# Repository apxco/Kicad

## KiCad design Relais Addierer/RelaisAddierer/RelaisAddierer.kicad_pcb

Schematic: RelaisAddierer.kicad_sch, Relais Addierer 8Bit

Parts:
A1: RaspberryPi_Pico; RaspberryPi_Pico_Common_Unspecified
C1: 1uF; C_0805_2012Metric_Pad1.18x1.45mm_HandSolder
C2, C3, C4, C5, C6, C7: 100nF; C_0805_2012Metric_Pad1.18x1.45mm_HandSolder
C8, C9, C10, C11, C12: 470uF; CP_Elec_10x12.5
D1, D2, D3, D4, D5, D6, D7, D8, D10, D11, D12, D13, D14, D15, D16, D17, D18, D19, D20, D21, D22, D23, D24, D25, D26, D27, D28, D29, D30, D31, D32, D33: 1N4148WT; D_SOD-523
D9: 1N4007; D_DO-41_SOD81_P10.16mm_Horizontal
J1: Conn_01x08_Pin; PinHeader_1x08_P2.54mm_Vertical
J2: Barrel_Jack; BarrelJack_GCT_DCJ200-10-A_Horizontal
K1, K2, K3, K4, K5, K6, K7, K8, K9, K10, K11, K12, K13, K14, K15, K16, K17, K18, K19, K20, K21, K22, K23, K24, K25, K26, K27, K28, K29, K30, K31, K32: HK19F-DCxxV-SHC; Relay_DPDT_Finder_30.22
R1, R2, R3, R4, R5, R6, R7, R8, R9, R10: 10k; R_0805_2012Metric_Pad1.20x1.40mm_HandSolder
SW1, SW2: RotaryEncoder_Switch; RotaryEncoder_Alps_EC12E-Switch_Vertical_H20mm
U1, U2, U3: TCA9534; TSSOP-16_4.4x5mm_P0.65mm
U4: uA7805; TO-263-2_TabPin1

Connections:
+5V: A1.40 (VBUS), C2.1, C3.1, C4.1, C5.1, C6.1, C7.1, J1.4, R1.1, R2.2, R3.2, R4.1, R5.2, R6.2, R7.1, R8.1, R9.1, R10.1, U1.16 (VDD), U2.1 (A0), U2.16 (VDD), U3.2 (A1), U3.16 (VDD), U4.3 (OUT)
+12V: C1.1, C8.1, C9.1, C10.1, C11.1, C12.1, D9.1 (K), K1.21, K6.11, K10.11, K14.11, K18.11, K20.11, K26.11, K28.11, U4.1 (IN)
Bit A.1: D2.1 (K), D4.1 (K), K1.A2, K4.A2
Bit A.2: D6.1 (K), D8.1 (K), K6.A2, K8.A2
Bit A.3: D20.1 (K), D24.1 (K), K18.A2, K22.A2
Bit A.4: D28.1 (K), D32.1 (K), K26.A2, K30.A2
Bit A.5: D11.1 (K), D13.1 (K), K10.A2, K12.A2
Bit A.6: D15.1 (K), D17.1 (K), K14.A2, K16.A2
Bit A.7: D22.1 (K), D25.1 (K), K20.A2, K24.A2
Bit A.8: D30.1 (K), D33.1 (K), K28.A2, K32.A2
Bit B.1: D1.1 (K), D3.1 (K), K2.A1, K3.A1
Bit B.2: D5.1 (K), D7.1 (K), K5.A1, K7.A1
Bit B.3: D18.1 (K), D21.1 (K), K17.A1, K21.A1
Bit B.4: D26.1 (K), D29.1 (K), K25.A1, K29.A1
Bit B.5: D10.1 (K), D12.1 (K), K9.A1, K11.A1
Bit B.6: D14.1 (K), D16.1 (K), K13.A1, K15.A1
Bit B.7: D19.1 (K), D23.1 (K), K19.A1, K23.A1
Bit B.8: D27.1 (K), D31.1 (K), K27.A1, K31.A1
CLK1: A1.21 (GPIO16), R1.2, R7.2, SW1.A
CLK2: A1.24 (GPIO18), R4.2, R9.2, SW2.A
Carry_Bit1: K2.11, K5.21, K6.21
Carry_Bit2: K5.11, K17.21, K18.21
Carry_Bit3: K17.11, K25.21, K26.21
Carry_Bit4: K9.21, K10.21, K25.11
Carry_Bit5: K9.11, K13.21, K14.21
Carry_Bit6: K13.11, K19.21, K20.21
Carry_Bit7: K19.11, K27.21, K28.21
Carry_Bit8: K27.11
DT1: A1.22 (GPIO17), R2.1, R8.2, SW1.B
DT2: A1.25 (GPIO19), R5.1, R10.2, SW2.B
GND: A1.3 (GND), A1.8 (GND), A1.13 (GND), A1.18 (GND), A1.23 (GND), A1.28 (GND), A1.33 (AGND), A1.38 (GND), C1.2, C2.2, C3.2, C4.2, C5.2, C6.2, C7.2, C8.2, C9.2, C10.2, C11.2, C12.2, D1.2 (A), D2.2 (A), D3.2 (A), D4.2 (A), D5.2 (A), D6.2 (A), D7.2 (A), D8.2 (A), D10.2 (A), D11.2 (A), D12.2 (A), D13.2 (A), D14.2 (A), D15.2 (A), D16.2 (A), D17.2 (A), D18.2 (A), D19.2 (A), D20.2 (A), D21.2 (A), D22.2 (A), D23.2 (A), D24.2 (A), D25.2 (A), D26.2 (A), D27.2 (A), D28.2 (A), D29.2 (A), D30.2 (A), D31.2 (A), D32.2 (A), D33.2 (A), J1.3, J2.2, K1.A1, K2.A2, K3.A2, K4.A1, K5.A2, K6.A1, K7.A2, K8.A1, K9.A2, K10.A1, K11.A2, K12.A1, K13.A2, K14.A1, K15.A2, K16.A1, K17.A2, K18.A1, K19.A2, K20.A1, K21.A2, K22.A1, K23.A2, K24.A1, K25.A2, K26.A1, K27.A2, K28.A1, K29.A2, K30.A1, K31.A2, K32.A1, SW1.C, SW1.S2, SW2.C, SW2.S2, U1.1 (A0), U1.2 (A1), U1.3 (A2), U1.8 (GND), U2.2 (A1), U2.3 (A2), U2.8 (GND), U3.1 (A0), U3.3 (A2), U3.8 (GND), U4.2 (GND)
I2C0 SCL: A1.27 (GPIO21), J1.5, U1.14 (SCL), U2.14 (SCL), U3.14 (SCL)
I2C0 SDA: A1.29 (GPIO22), J1.6, U1.15 (SDA), U2.15 (SDA), U3.15 (SDA)
unnamed: D9.2 (A), J2.1
unnamed: K1.12, K3.22, K4.14
unnamed: K1.14, K1.22, K2.14
unnamed: K1.24, K2.12
unnamed: K2.22, K3.14, K4.22
unnamed: K2.24, K3.12, K4.24
unnamed: K3.11, K4.11
unnamed: K3.24, K4.12
unnamed: K5.12, K6.24
unnamed: K5.14, K6.14, K6.22
unnamed: K5.22, K7.14, K8.22
unnamed: K5.24, K7.12, K8.24
unnamed: K6.12, K7.22, K8.14
unnamed: K7.11, K8.11
unnamed: K7.24, K8.12
unnamed: K10.12, K11.22, K12.14
unnamed: K9.14, K10.14, K10.22
unnamed: K9.12, K10.24
unnamed: K11.11, K12.11
unnamed: K9.24, K11.12, K12.24
unnamed: K9.22, K11.14, K12.22
unnamed: K11.24, K12.12
unnamed: K13.12, K14.24
unnamed: K13.14, K14.14, K14.22
unnamed: K13.22, K15.14, K16.22
unnamed: K13.24, K15.12, K16.24
unnamed: K14.12, K15.22, K16.14
unnamed: K15.11, K16.11
unnamed: K15.24, K16.12
unnamed: K17.12, K18.24
unnamed: K17.14, K18.14, K18.22
unnamed: K17.22, K21.14, K22.22
unnamed: K17.24, K21.12, K22.24
unnamed: K18.12, K21.22, K22.14
unnamed: K19.12, K20.24
unnamed: K19.14, K20.14, K20.22
unnamed: K19.22, K23.14, K24.22
unnamed: K19.24, K23.12, K24.24
unnamed: K20.12, K23.22, K24.14
unnamed: K21.11, K22.11
unnamed: K21.24, K22.12
unnamed: K23.11, K24.11
unnamed: K23.24, K24.12
unnamed: K25.12, K26.24
unnamed: K25.14, K26.14, K26.22
unnamed: K25.22, K29.14, K30.22
unnamed: K25.24, K29.12, K30.24
unnamed: K26.12, K29.22, K30.14
unnamed: K27.12, K28.24
unnamed: K27.14, K28.14, K28.22
unnamed: K27.22, K31.14, K32.22
unnamed: K27.24, K31.12, K32.24
unnamed: K28.12, K31.22, K32.14
unnamed: K29.11, K30.11
unnamed: K29.24, K30.12
unnamed: K31.11, K32.11
unnamed: K31.24, K32.12
Summ_Bit1: K4.21
Summ_Bit2: K8.21
Summ_Bit3: K22.21
Summ_Bit4: K30.21
Summ_Bit5: K12.21
Summ_Bit6: K16.21
Summ_Bit7: K24.21
Summ_Bit8: K32.21

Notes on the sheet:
0x21
Byte A
0x22
Byte B
Byte A
Ergebnis Eingang
0x20
0x3c
Relais HK19F-DC12V-SHG Spule 12V 12,5mA bis 30mA Stromaufnahme Benötigt 32 Relais Netzteil 12 V bei 20mA Mittlerer Stromaufnahme und 32 Relais 640mA

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
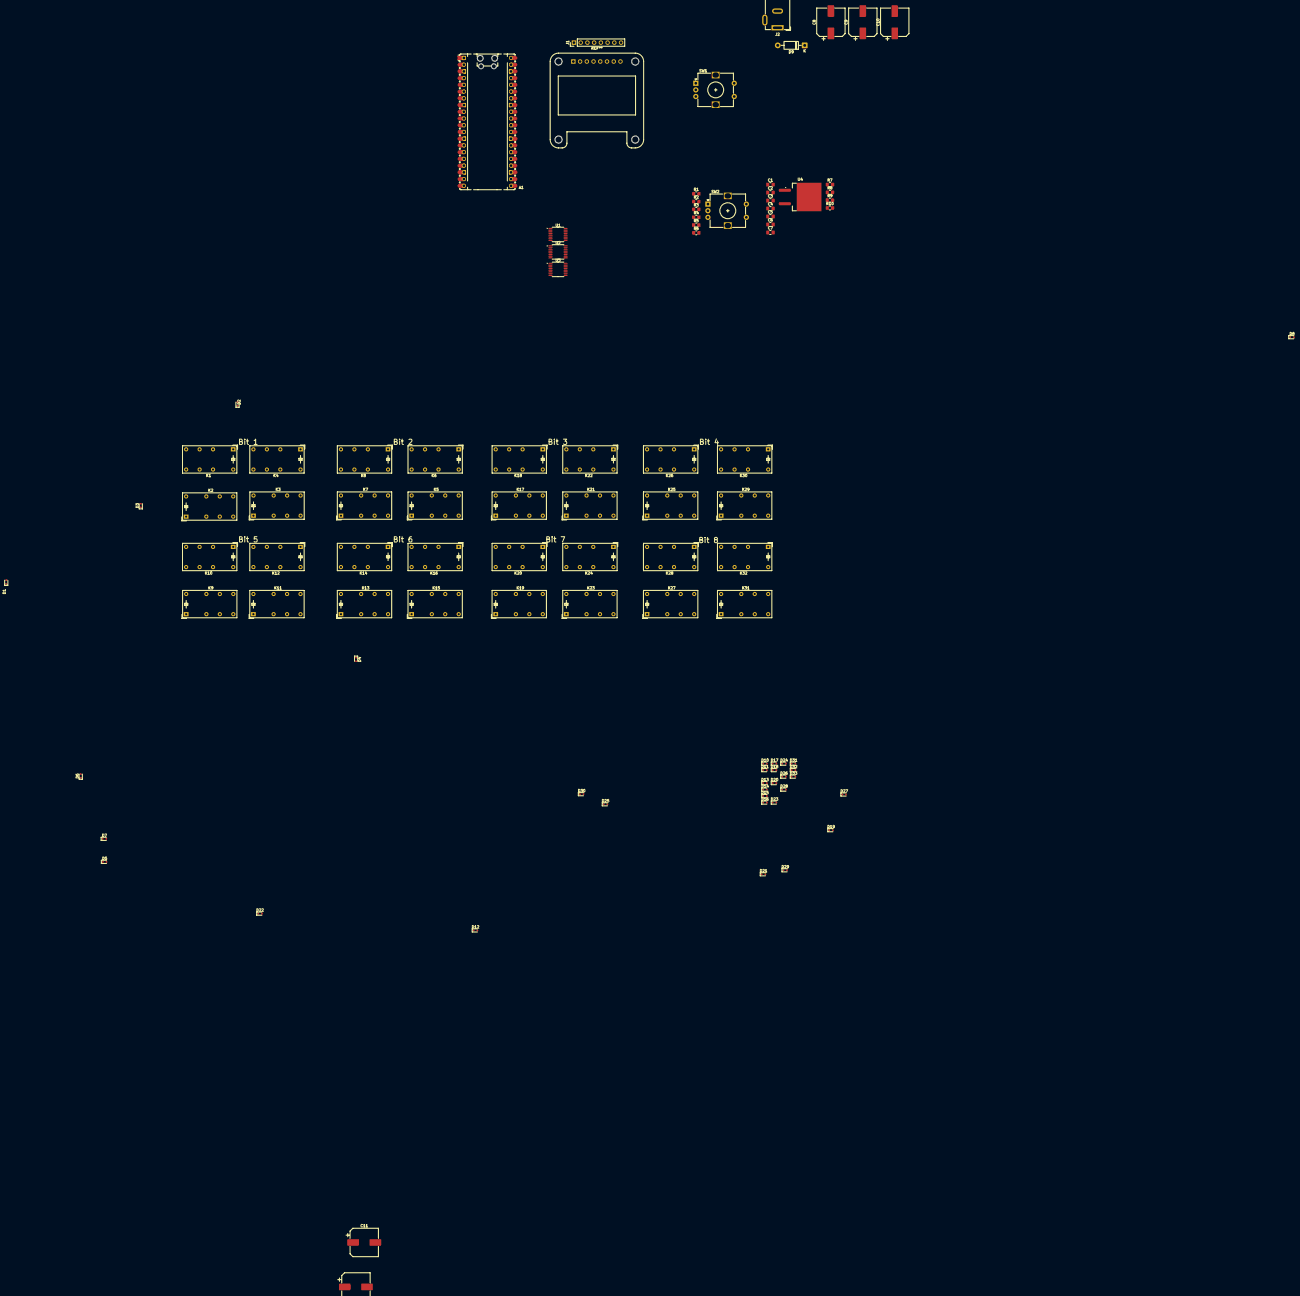
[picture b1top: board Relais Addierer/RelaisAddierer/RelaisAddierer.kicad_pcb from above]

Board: 2 copper layers, 96 parts (0 on the bottom side), 90 nets, no tracks yet.

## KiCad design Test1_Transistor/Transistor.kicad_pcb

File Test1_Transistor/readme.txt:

Zum Testen von einigen Transistorschaltungen für Verstärker. Noch nicht fertig.

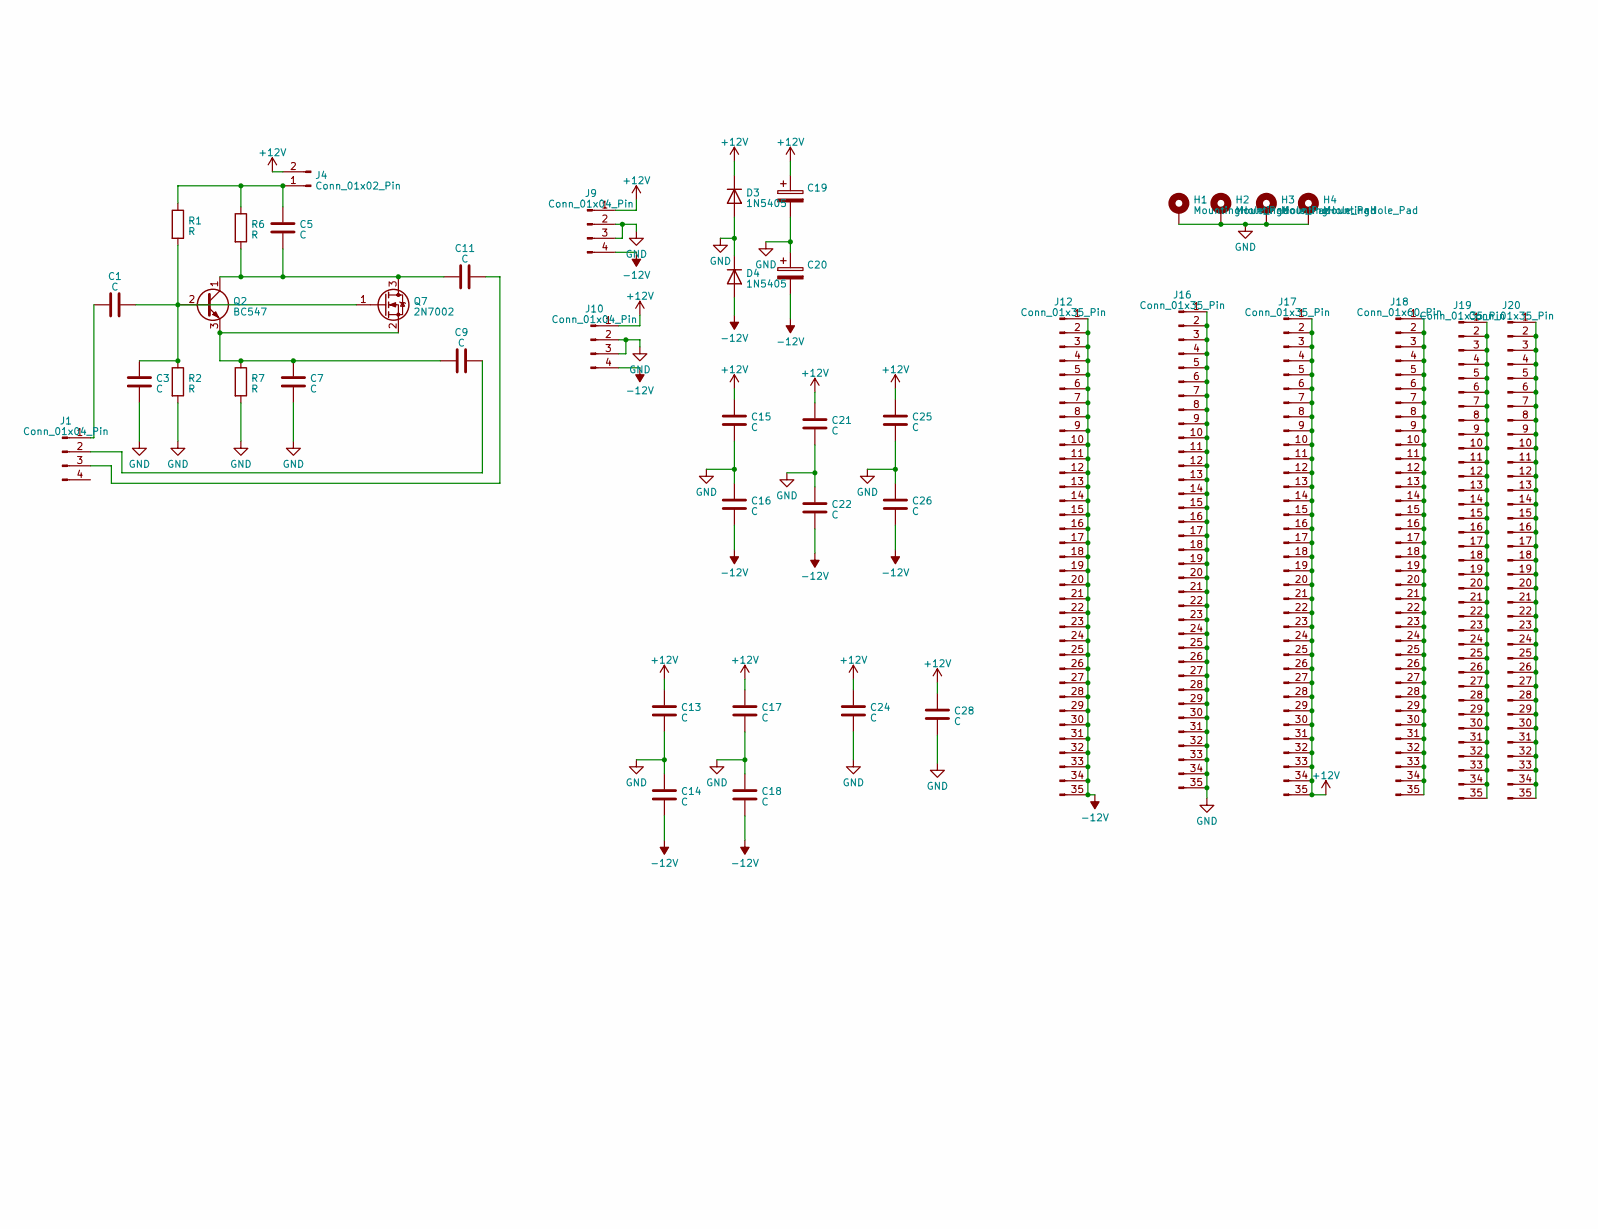
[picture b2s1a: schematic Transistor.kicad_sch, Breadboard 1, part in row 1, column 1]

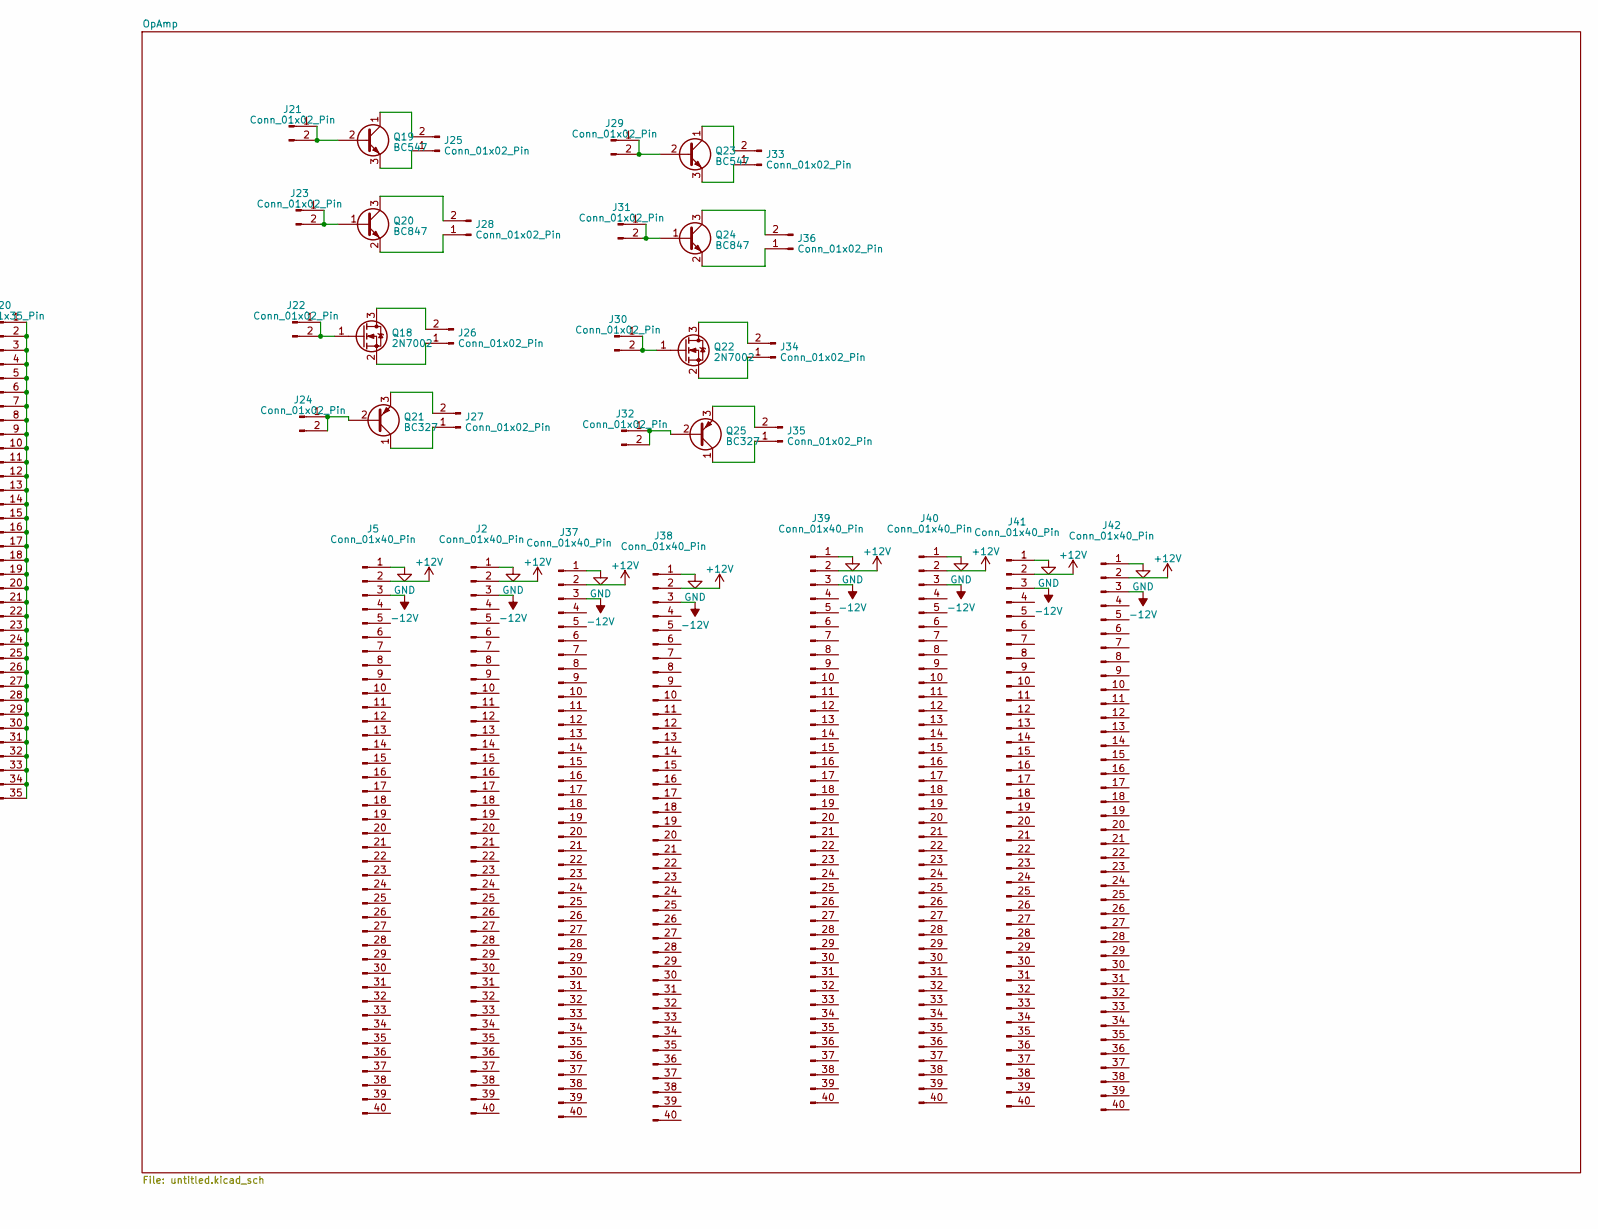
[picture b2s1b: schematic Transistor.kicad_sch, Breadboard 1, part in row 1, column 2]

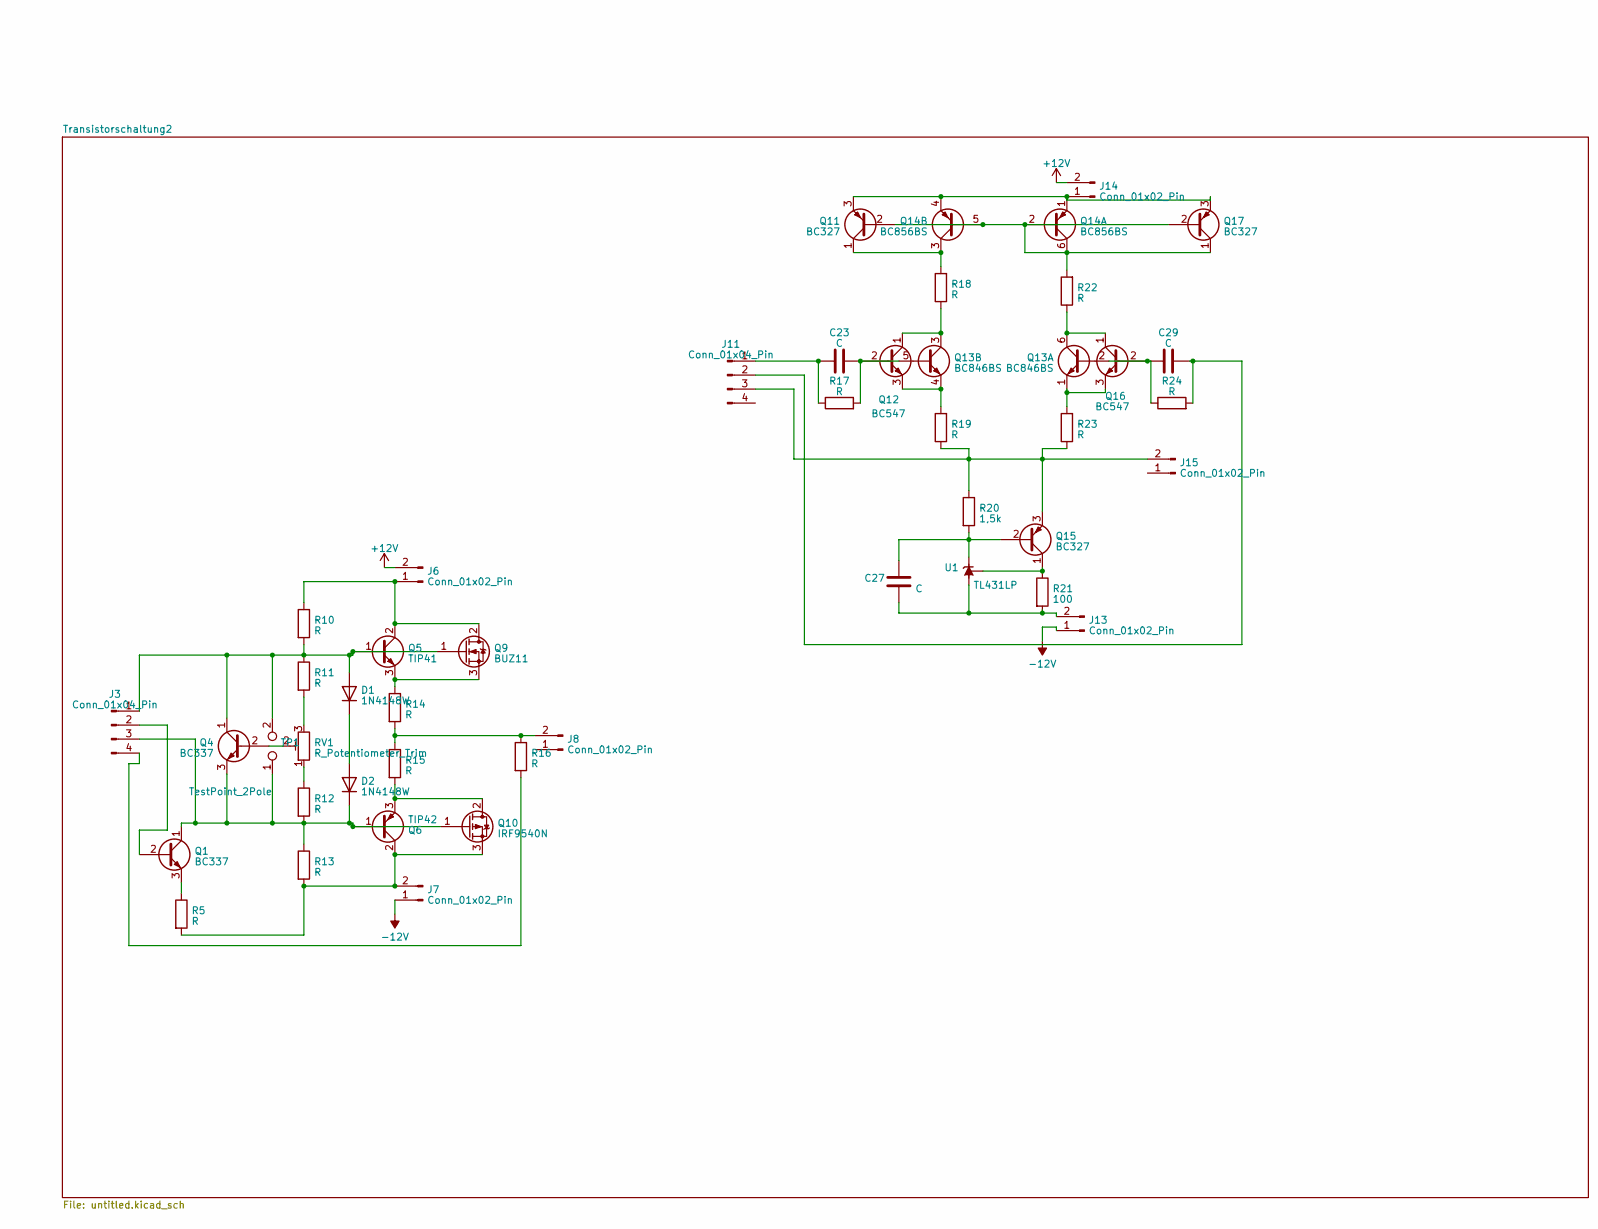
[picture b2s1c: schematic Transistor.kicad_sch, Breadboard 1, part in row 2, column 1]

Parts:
C1, C3, C5, C7, C9, C11, C13, C14, C15, C16, C17, C18, C21, C22, C23, C24, C25, C26, C27, C28, C29: C; C_0805_2012Metric_Pad1.18x1.45mm_HandSolder
C19, C20: C_Polarized; CP_Elec_6.3x5.9
D1, D2: 1N4148W; D_SOD-123
D3, D4: 1N5405; D_DO-201AD_P15.24mm_Horizontal
H1, H2, H3, H4: MountingHole_Pad; MountingHole_3.2mm_M3_DIN965_Pad_TopBottom
J1, J3: Conn_01x04_Pin; PinHeader_1x04_P1.27mm_Vertical
J2, J5, J37, J38, J39, J40, J41, J42: Conn_01x40_Pin; PinSocket_1x40_P1.27mm_Vertical
J4, J6, J7, J8, J14: Conn_01x02_Pin; PinSocket_1x02_P1.27mm_Vertical
J9, J10, J11: Conn_01x04_Pin; PinSocket_1x04_P1.27mm_Vertical
J12, J16, J17, J19, J20: Conn_01x35_Pin; PinSocket_1x35_P1.27mm_Vertical
J13, J15, J21, J22, J23, J24, J25, J26, J27, J28, J29, J30, J31, J32, J33, J34, J35, J36: Conn_01x02_Pin; PinHeader_1x02_P1.27mm_Vertical
J18: Conn_01x60_Pin; PinSocket_1x35_P1.27mm_Vertical
Q1, Q4: BC337; TO-92_Inline
Q2, Q12, Q16, Q19, Q23: BC547; TO-92_Inline
Q5: TIP41; TO-220-3_Vertical
Q6: TIP42; TO-220-3_Vertical
Q7, Q18, Q22: 2N7002; SOT-23
Q9: BUZ11; TO-220-3_Vertical
Q10: IRF9540N; TO-220-3_Vertical
Q11, Q15, Q17, Q21, Q25: BC327; TO-92_Inline
Q13: BC846BS; SOT-363_SC-70-6
Q14: BC856BS; SOT-363_SC-70-6
Q20, Q24: BC847; SOT-23
R1, R2, R5, R6, R7, R10, R11, R12, R13, R16, R17, R18, R19, R22, R23, R24: R; R_0805_2012Metric_Pad1.20x1.40mm_HandSolder
R14, R15: R; R_2512_6332Metric_Pad1.40x3.35mm_HandSolder
R20: 1,5k; R_0805_2012Metric_Pad1.20x1.40mm_HandSolder
R21: 100; R_0805_2012Metric_Pad1.20x1.40mm_HandSolder
RV1: R_Potentiometer_Trim; Potentiometer_Bourns_3266Y_Vertical
TP1: TestPoint_2Pole; PinHeader_2x01_P1.27mm_Vertical
U1: TL431LP; TO-92_Inline

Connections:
+12V: C13.1, C15.1, C17.1, C19.1, C21.1, C24.1, C25.1, C28.1, D3.1 (K), J2.2, J4.2, J5.2, J6.2, J9.1, J10.1, J14.2, J17.1, J17.2, J17.3, J17.4, J17.5, J17.6, J17.7, J17.8, J17.9, J17.10, J17.11, J17.12, J17.13, J17.14, J17.15, J17.16, J17.17, J17.18, J17.19, J17.20, J17.21, J17.22, J17.23, J17.24, J17.25, J17.26, J17.27, J17.28, J17.29, J17.30, J17.31, J17.32, J17.33, J17.34, J17.35, J37.2, J38.2, J39.2, J40.2, J41.2, J42.2
-12V: C14.2, C16.2, C18.2, C20.2, C22.2, C26.2, D4.2 (A), J2.3, J5.3, J7.1, J9.4, J10.4, J12.1, J12.2, J12.3, J12.4, J12.5, J12.6, J12.7, J12.8, J12.9, J12.10, J12.11, J12.12, J12.13, J12.14, J12.15, J12.16, J12.17, J12.18, J12.19, J12.20, J12.21, J12.22, J12.23, J12.24, J12.25, J12.26, J12.27, J12.28, J12.29, J12.30, J12.31, J12.32, J12.33, J12.34, J12.35, J13.1, J37.3, J38.3, J39.3, J40.3, J41.3, J42.3
GND: C3.2, C7.2, C13.2, C14.1, C15.2, C16.1, C17.2, C18.1, C19.2, C20.1, C21.2, C22.1, C24.2, C25.2, C26.1, C28.2, D3.2 (A), D4.1 (K), H1.1, H2.1, H3.1, H4.1, J2.1, J5.1, J9.2, J9.3, J10.2, J10.3, J16.1, J16.2, J16.3, J16.4, J16.5, J16.6, J16.7, J16.8, J16.9, J16.10, J16.11, J16.12, J16.13, J16.14, J16.15, J16.16, J16.17, J16.18, J16.19, J16.20, J16.21, J16.22, J16.23, J16.24, J16.25, J16.26, J16.27, J16.28, J16.29, J16.30, J16.31, J16.32, J16.33, J16.34, J16.35, J37.1, J38.1, J39.1, J40.1, J41.1, J42.1, R2.2, R7.2
unnamed: D1.2 (A), J3.1, Q4.1 (C), Q5.1 (B), Q9.1 (G), R10.2, R11.1, TP1.2
unnamed: D1.1 (K), D2.2 (A)
unnamed: D2.1 (K), J3.3, Q1.1 (C), Q4.3 (E), Q6.1 (B), Q10.1 (G), R12.2, R13.1, TP1.1
unnamed: C1.1, J1.1
unnamed: C9.1, J1.2
unnamed: C11.1, J1.3
unnamed: J3.2, Q1.2 (B)
unnamed: J3.4, R16.2
unnamed: C5.2, J4.1, R1.1, R6.1
unnamed: J6.1, Q5.2 (C), Q9.2 (D), R10.1
unnamed: J7.2, Q6.2 (C), Q10.3 (S), R5.2, R13.2
unnamed: J8.2, R14.2, R15.1, R16.1
unnamed: C23.1, J11.1, R17.1
unnamed: C29.2, J11.2, R24.2
unnamed: J11.3, J15.2, Q15.3 (E), R19.1, R20.1, R23.1
unnamed: C27.1, J13.2, R21.2, U1.2 (A)
unnamed: J14.1, Q11.3 (E), Q14.1 (E1), Q14.4 (E2), Q17.3 (E)
unnamed: J18.1, J18.2, J18.3, J18.4, J18.5, J18.6, J18.7, J18.8, J18.9, J18.10, J18.11, J18.12, J18.13, J18.14, J18.15, J18.16, J18.17, J18.18, J18.19, J18.20, J18.21, J18.22, J18.23, J18.24, J18.25, J18.26, J18.27, J18.28, J18.29, J18.30, J18.31, J18.32, J18.33, J18.34, J18.35
unnamed: J19.1, J19.2, J19.3, J19.4, J19.5, J19.6, J19.7, J19.8, J19.9, J19.10, J19.11, J19.12, J19.13, J19.14, J19.15, J19.16, J19.17, J19.18, J19.19, J19.20, J19.21, J19.22, J19.23, J19.24, J19.25, J19.26, J19.27, J19.28, J19.29, J19.30, J19.31, J19.32, J19.33, J19.34, J19.35
unnamed: J20.1, J20.2, J20.3, J20.4, J20.5, J20.6, J20.7, J20.8, J20.9, J20.10, J20.11, J20.12, J20.13, J20.14, J20.15, J20.16, J20.17, J20.18, J20.19, J20.20, J20.21, J20.22, J20.23, J20.24, J20.25, J20.26, J20.27, J20.28, J20.29, J20.30, J20.31, J20.32, J20.33, J20.34, J20.35
unnamed: J21.1, J21.2, Q19.2 (B)
unnamed: J22.1, J22.2, Q18.1 (G)
unnamed: J23.1, J23.2, Q20.1 (B)
unnamed: J24.1, J24.2, Q21.2 (B)
unnamed: J25.1, Q19.3 (E)
unnamed: J25.2, Q19.1 (C)
unnamed: J26.1, Q18.2 (S)
unnamed: J26.2, Q18.3 (D)
unnamed: J27.1, Q21.1 (C)
unnamed: J27.2, Q21.3 (E)
unnamed: J28.1, Q20.2 (E)
unnamed: J28.2, Q20.3 (C)
unnamed: J29.1, J29.2, Q23.2 (B)
unnamed: J30.1, J30.2, Q22.1 (G)
unnamed: J31.1, J31.2, Q24.1 (B)
unnamed: J32.1, J32.2, Q25.2 (B)
unnamed: J33.1, Q23.3 (E)
unnamed: J33.2, Q23.1 (C)
unnamed: J34.1, Q22.2 (S)
unnamed: J34.2, Q22.3 (D)
unnamed: J35.1, Q25.1 (C)
unnamed: J35.2, Q25.3 (E)
unnamed: J36.1, Q24.2 (E)
unnamed: J36.2, Q24.3 (C)
unnamed: Q1.3 (E), R5.1
unnamed: C1.2, C3.1, Q2.2 (B), Q7.1 (G), R1.2, R2.1
unnamed: C5.1, C11.2, Q2.1 (C), Q7.3 (D), R6.2
unnamed: C7.1, C9.2, Q2.3 (E), Q7.2 (S), R7.1
unnamed: Q4.2 (B), RV1.2
unnamed: Q5.3 (E), Q9.3 (S), R14.1
unnamed: Q6.3 (E), Q10.2 (D), R15.2
unnamed: Q11.2 (B), Q14.2 (B1), Q14.5 (B2), Q14.6 (C1), Q17.1 (C), Q17.2 (B), R22.2
unnamed: Q11.1 (C), Q14.3 (C2), R18.2
unnamed: C23.2, Q12.2 (B), Q13.5 (B2), R17.2
unnamed: Q12.1 (C), Q13.3 (C2), R18.1
unnamed: Q12.3 (E), Q13.4 (E2), R19.2
unnamed: C29.1, Q13.2 (B1), Q16.2 (B), R24.1
unnamed: Q13.6 (C1), Q16.1 (C), R22.1
unnamed: Q13.1 (E1), Q16.3 (E), R23.2
unnamed: C27.2, Q15.2 (B), R20.2, U1.3 (K)
unnamed: Q15.1 (C), R21.1, U1.1 (REF)
unnamed: R11.2, RV1.3
unnamed: R12.1, RV1.1

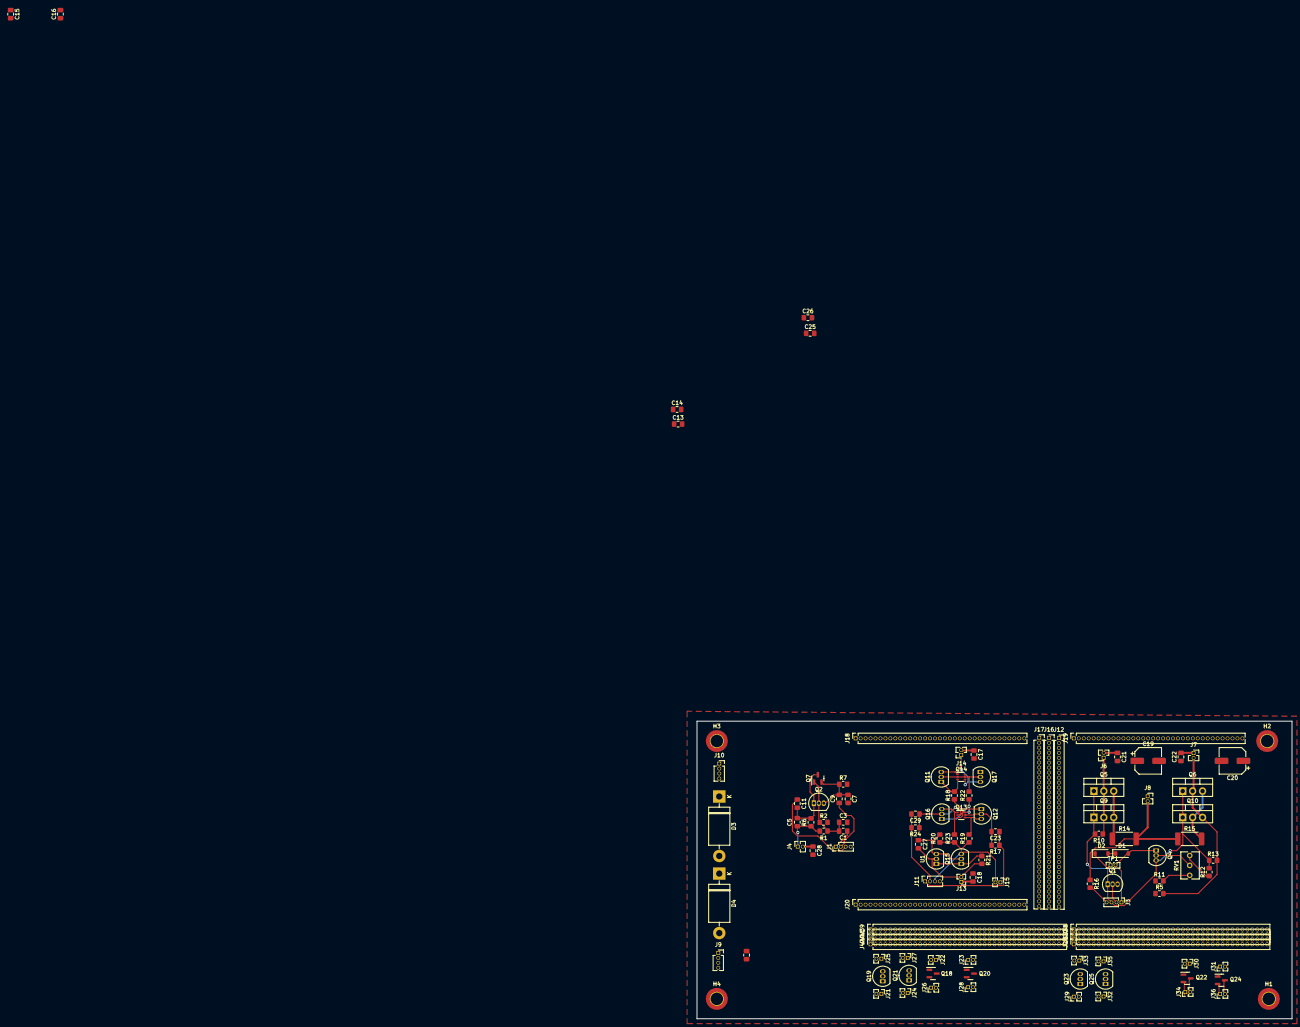
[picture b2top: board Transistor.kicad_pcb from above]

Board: 2 copper layers, 152.4 x 76.2 mm, 119 parts (0 on the bottom side), 66 nets.

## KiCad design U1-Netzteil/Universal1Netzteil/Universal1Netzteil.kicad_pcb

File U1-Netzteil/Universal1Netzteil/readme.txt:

Platine für Kleintransformatoren die ich rumliegen hatte. Ersatz füer einen Lochrasteraufbau.
In dieser Version in 2025 Platine hergestellt und ausprobiert, funktioniert wie erwartet.

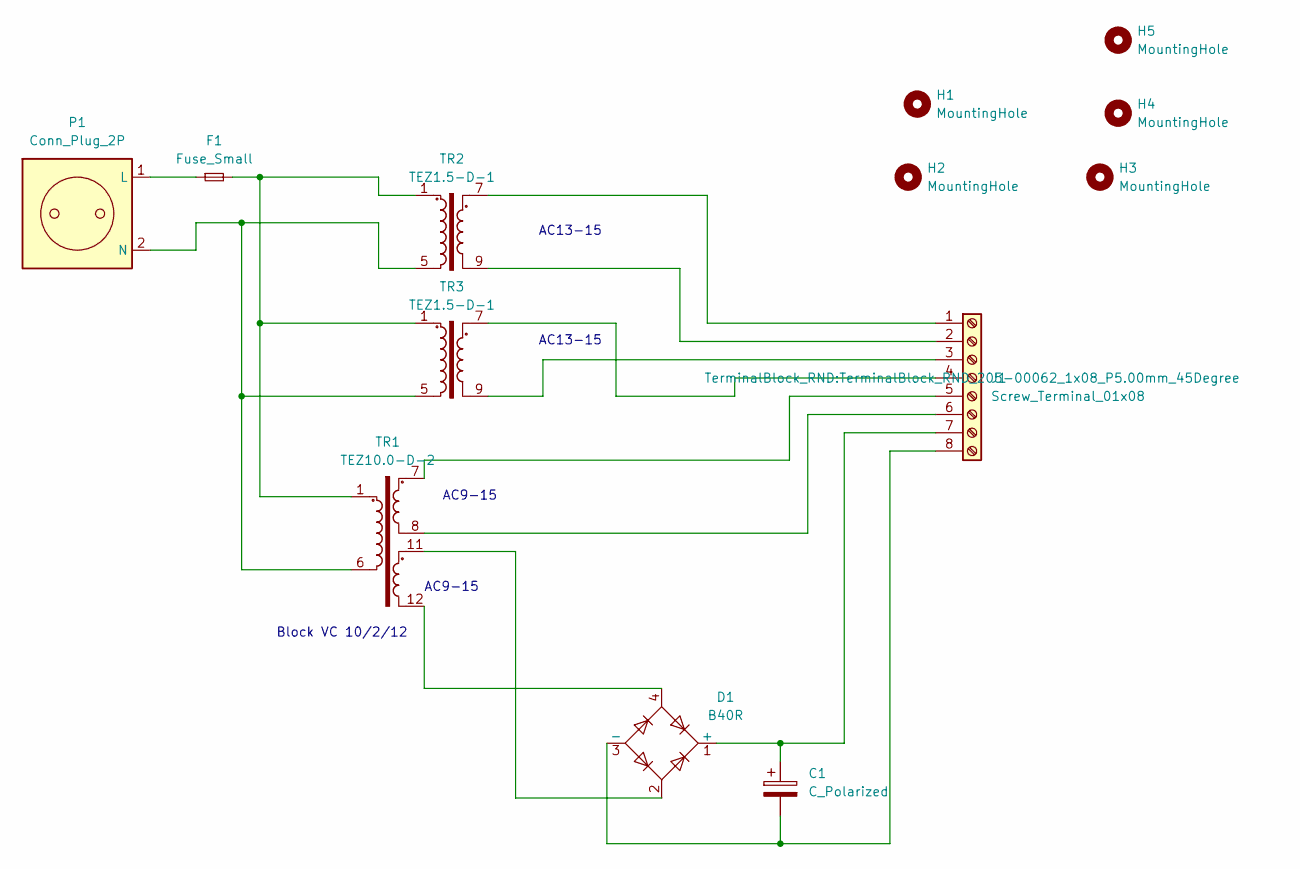
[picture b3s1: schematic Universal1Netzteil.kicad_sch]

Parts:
C1: C_Polarized; CP_Radial_D13.0mm_P7.50mm
D1: B40R; Diode_Bridge_Round_D9.0mm
F1: Fuse_Small; Fuse_Littelfuse_372_D8.50mm
H1, H2, H3, H4, H5: MountingHole; MountingHole_3.5mm_Pad
J1: Screw_Terminal_01x08; TerminalBlock_RND_205-00062_1x08_P5.00mm_45Degree
P1: Conn_Plug_2P; SolderWire-0.75sqmm_1x02_P7mm_D1.25mm_OD3.5mm_Relief
TR1: TEZ10.0-D-2; Transformer_CHK_EI48-8VA_2xSec
TR2, TR3: TEZ1.5-D-1; Transformer_CHK_EI38-3VA_1xSec

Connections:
unnamed: C1.1, D1.1 (+), J1.7
unnamed: C1.2, D1.3 (-), J1.8
unnamed: D1.2, TR1.11
unnamed: D1.4, TR1.12
unnamed: F1.2, TR1.1, TR2.1, TR3.1
unnamed: J1.1, TR2.7
unnamed: J1.2, TR2.9
unnamed: J1.3, TR3.9
unnamed: J1.4, TR3.7
unnamed: J1.5, TR1.7
unnamed: J1.6, TR1.8
unnamed: F1.1, P1.1 (L)
unnamed: P1.2 (N), TR1.6, TR2.5, TR3.5

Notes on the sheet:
AC13-15
AC9-15
Block VC 10/2/12

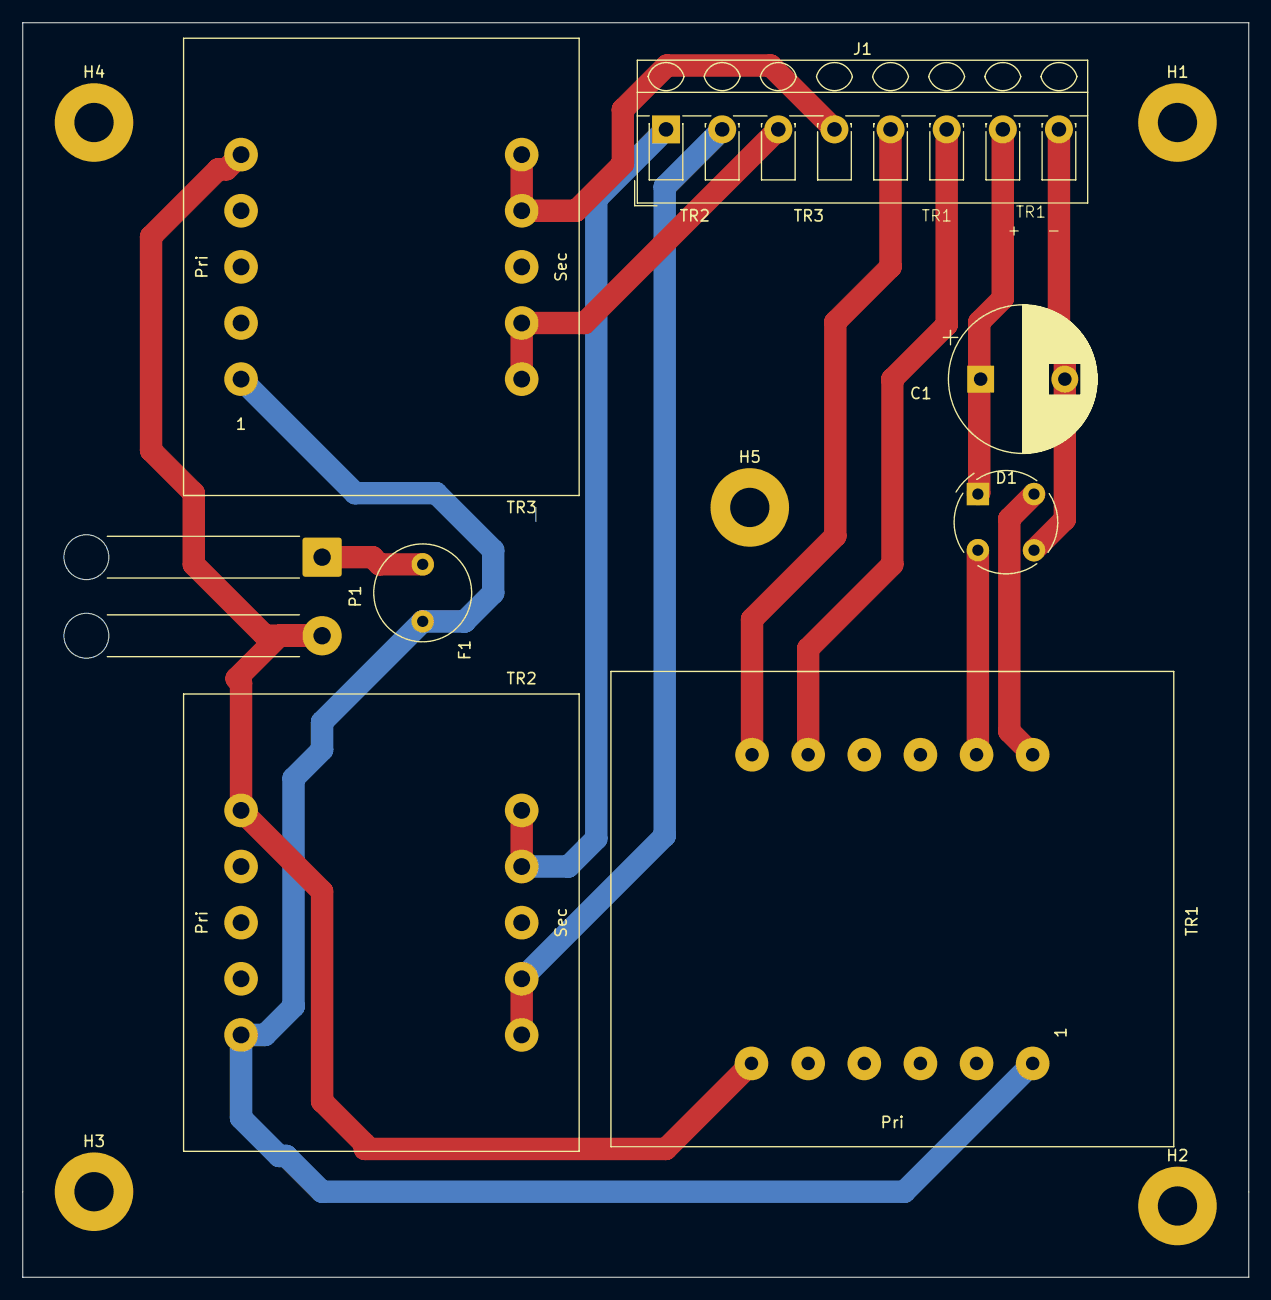
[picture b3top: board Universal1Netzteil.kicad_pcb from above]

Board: 2 copper layers, 109.2 x 111.8 mm, 13 parts (0 on the bottom side), 13 nets.
